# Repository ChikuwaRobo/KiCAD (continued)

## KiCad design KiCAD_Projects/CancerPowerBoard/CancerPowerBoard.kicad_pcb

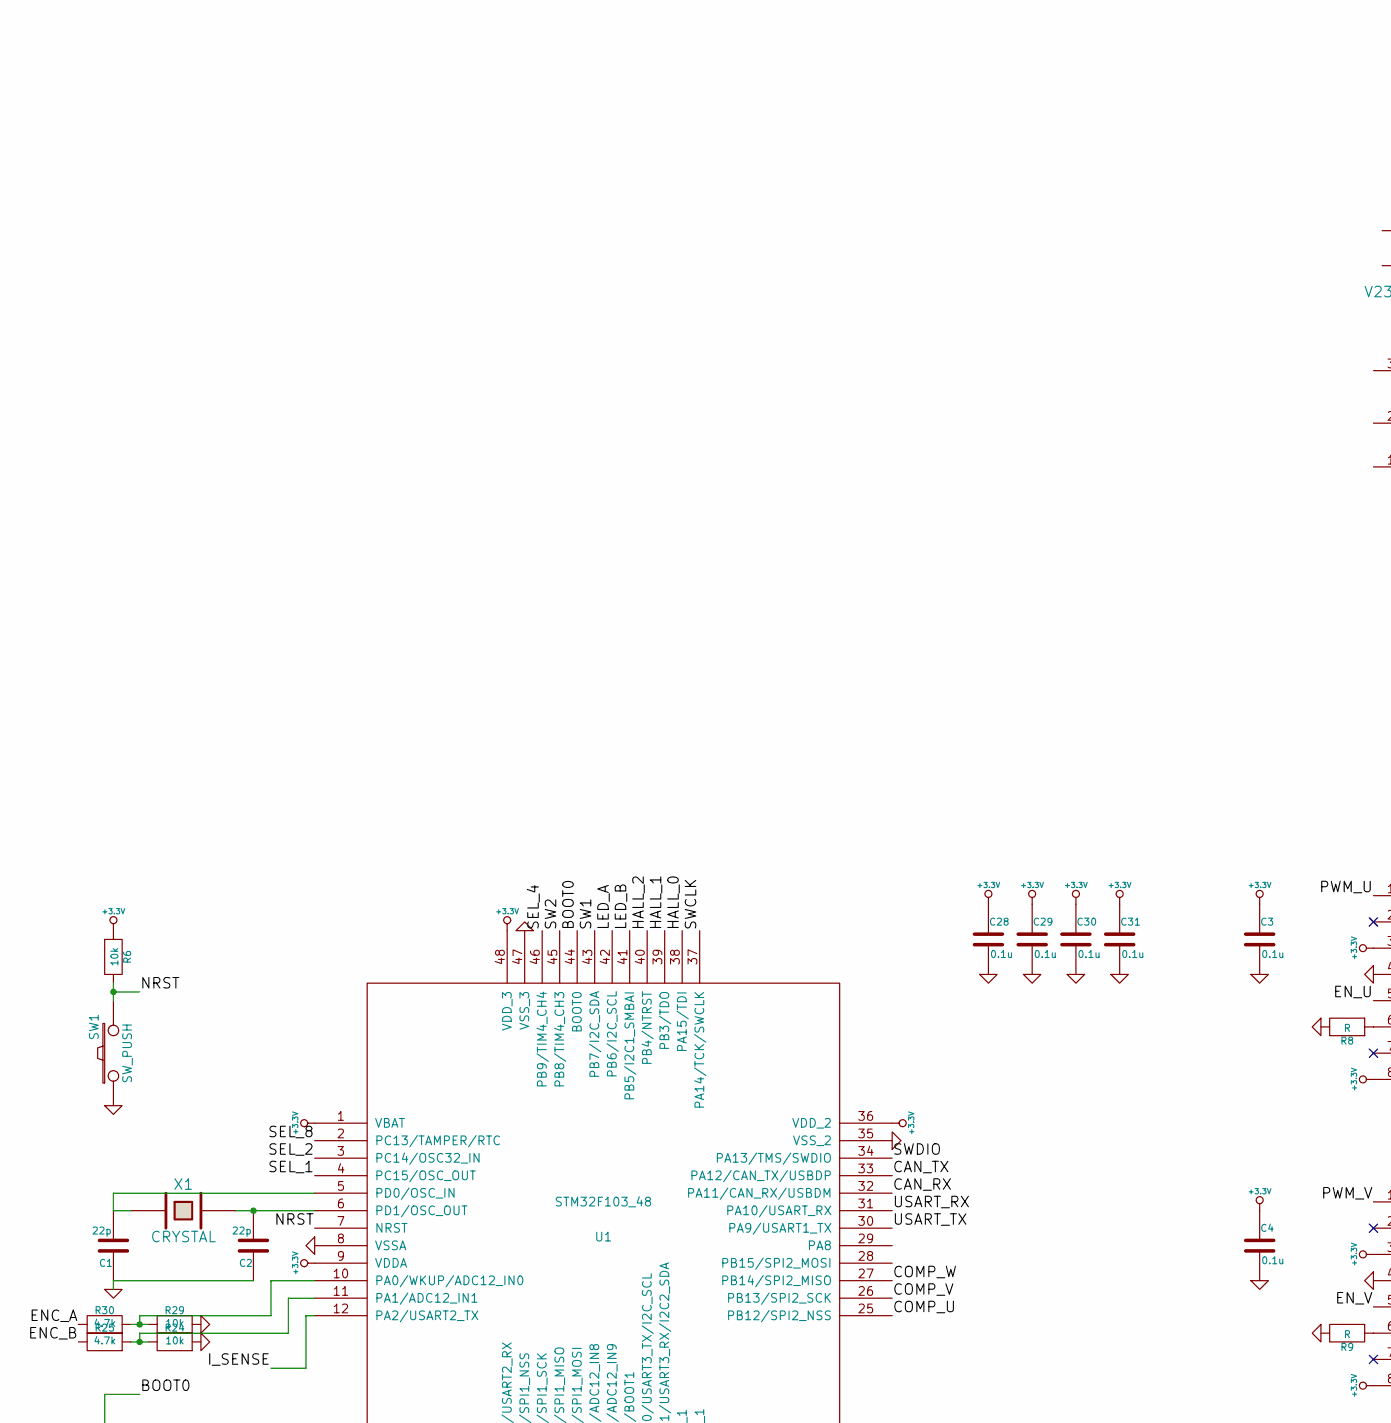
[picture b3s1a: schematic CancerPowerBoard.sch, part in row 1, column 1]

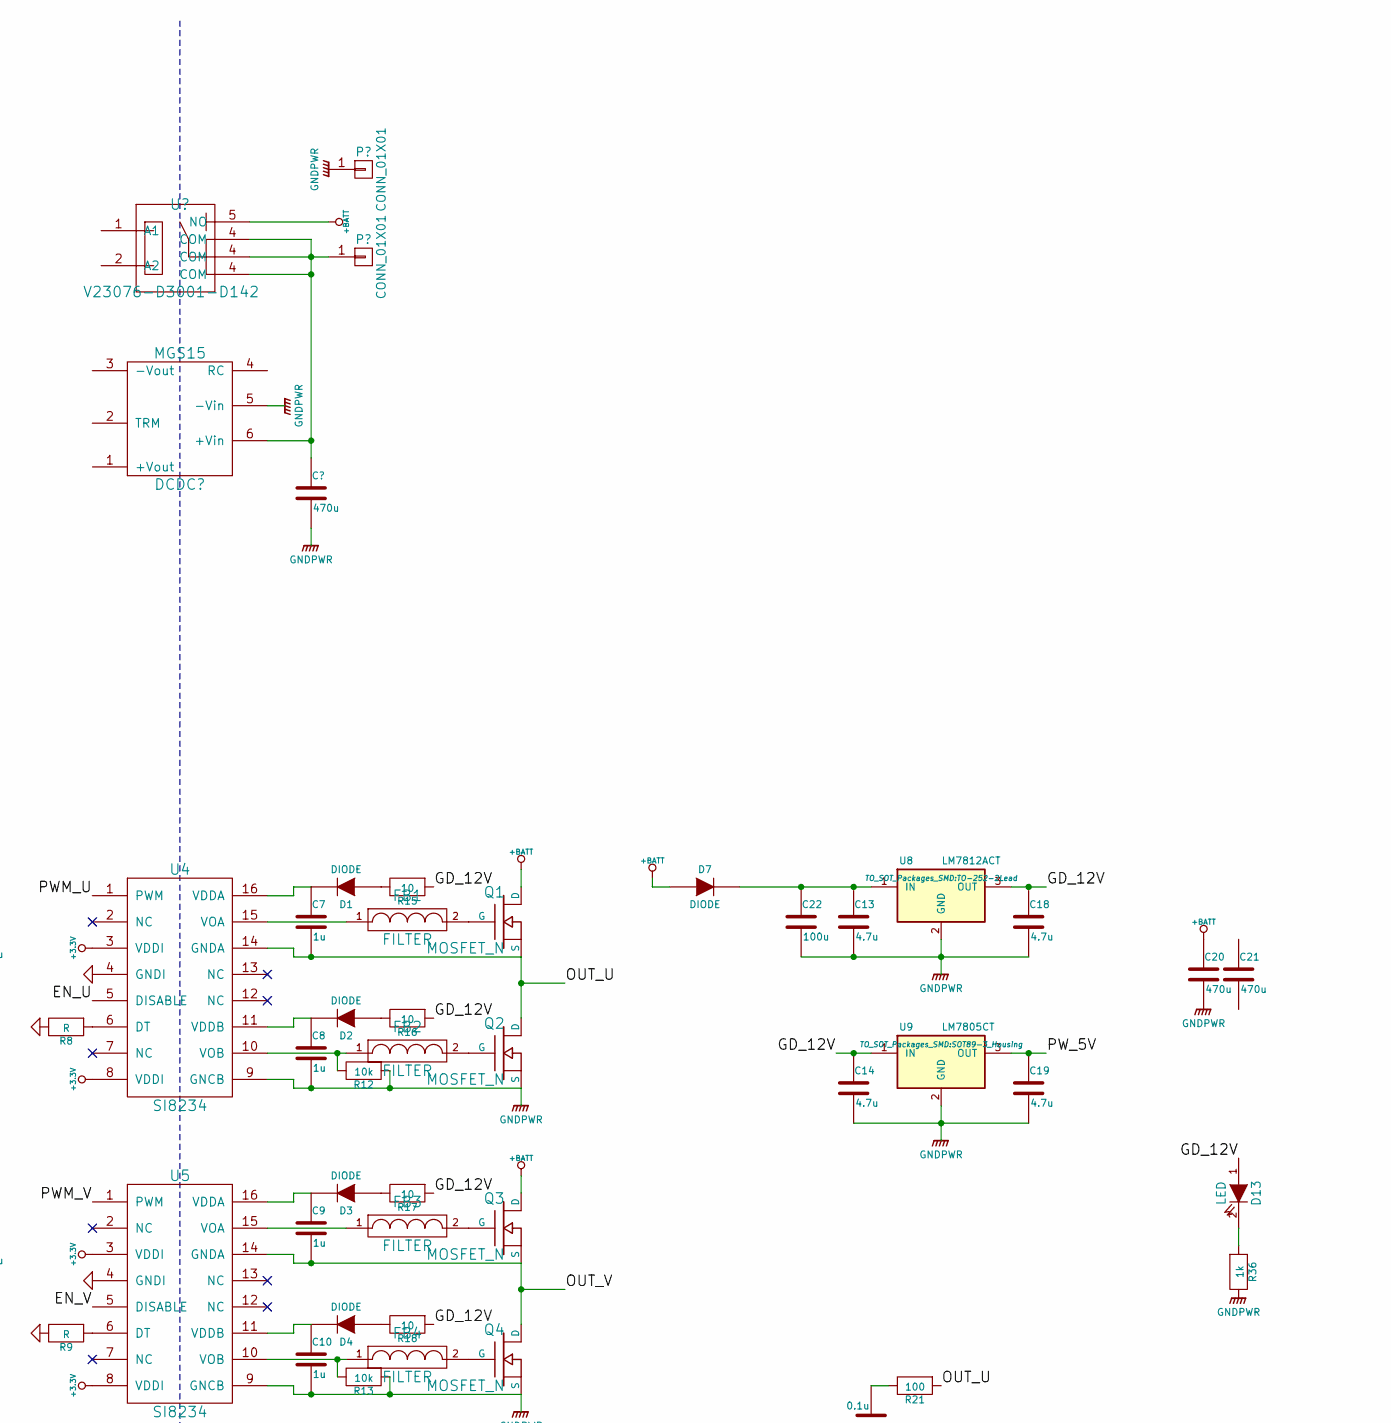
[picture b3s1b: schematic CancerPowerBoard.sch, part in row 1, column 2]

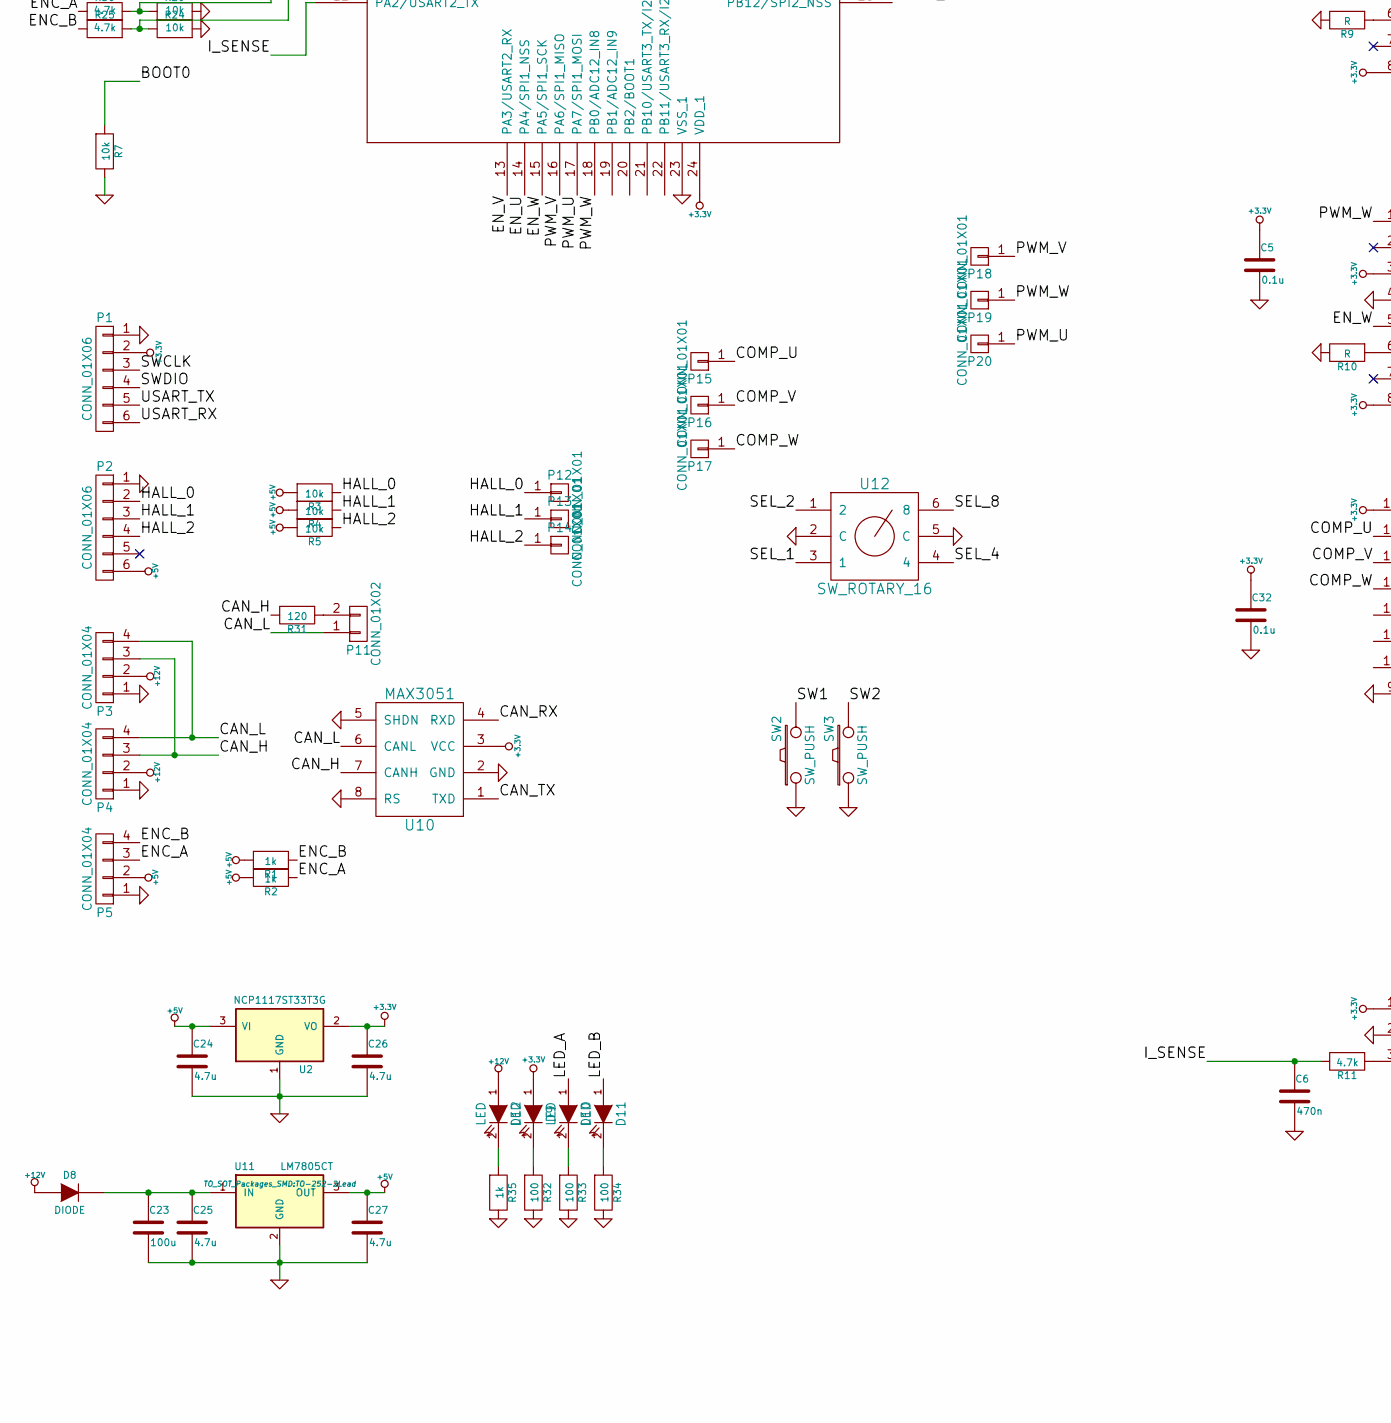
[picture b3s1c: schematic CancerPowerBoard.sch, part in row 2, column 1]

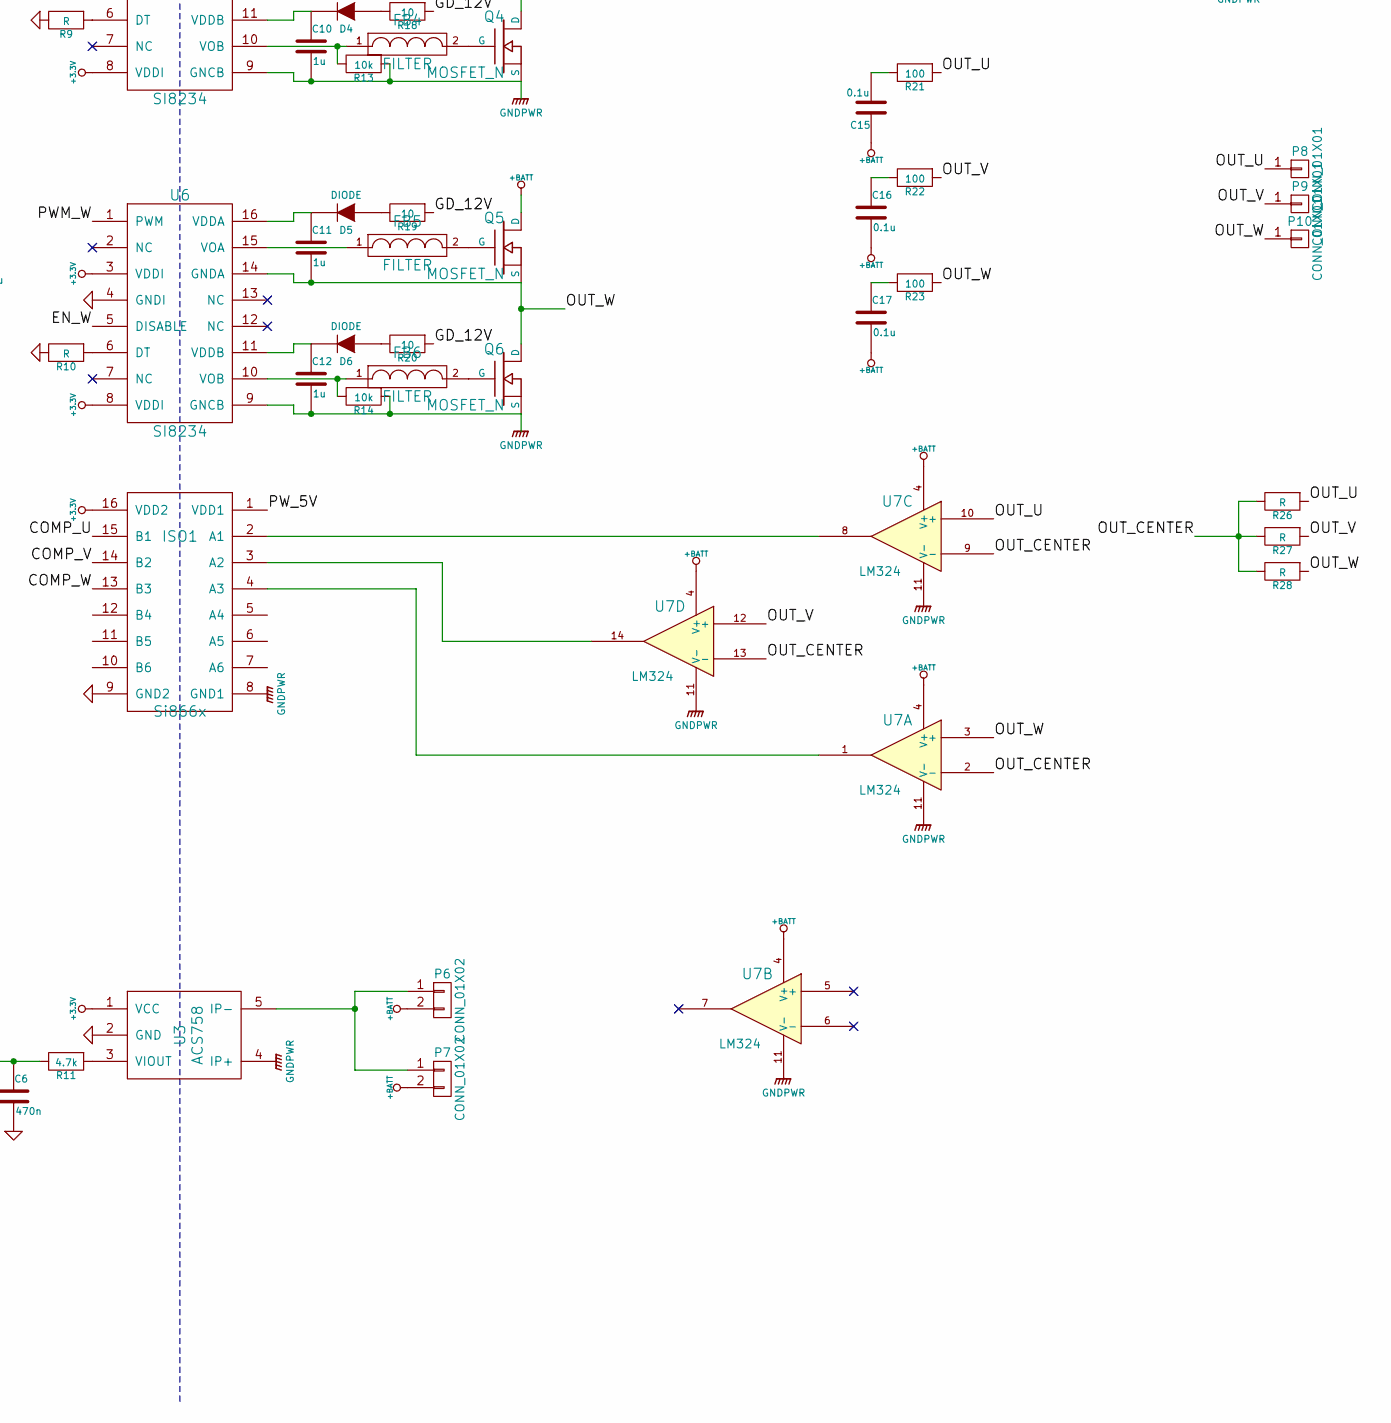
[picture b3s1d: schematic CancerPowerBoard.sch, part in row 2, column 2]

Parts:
C1, C2: 22p; C1608_WP
C3, C4, C5, C15, C16, C17, C28, C29, C30, C31, C32: 0.1u; C1608_WP
C6: 470n; C1608_WP
C7, C8, C9, C10, C11, C12: 1u; C3216
C13, C14, C18, C19, C24, C25, C26, C27: 4.7u; C3216
C20, C21: 470u; c_elec_10x10.5
C22, C23: 100u; C_Radial_D6.3_L11.2_P2.5
D1, D2, D3, D4, D5, D6: DIODE; C1608_WP
D7, D8: DIODE; C3216
D9, D10, D11, D12, D13: LED; LED_0805
FB1, FB2, FB3, FB4, FB5, FB6: FILTER; C1608_WP
ISO1: Si866x; SOIC-16_3.9x9.9mm_Pitch1.27mm
P1, P2: CONN_01X06; ZH_6T
P3, P4, P5: CONN_01X04; XA_4LC
P6: CONN_01X02; DEANS_T_F
P7: CONN_01X02; DEANS_T_M
P8, P9, P10: CONN_01X01; 1pin
P11: CONN_01X02; Pin_Header_Straight_1x02
P12, P13, P14, P15, P16, P17, P18, P19, P20: CONN_01X01; PINTST
Q1, Q2, Q3, Q4, Q5, Q6: MOSFET_N; HSOF-8-1
R1, R2, R35, R36: 1k; C1608_WP
R3, R4, R5, R6, R7, R12, R13, R14, R24, R29: 10k; C1608_WP
R8, R9, R10, R26, R27, R28: R; C1608_WP
R11, R25, R30: 4.7k; C1608_WP
R15, R16, R17, R18, R19, R20: 10; C1608_WP
R21, R22, R23, R32, R33, R34: 100; C1608_WP
R31: 120; C1608_WP
SW1, SW2, SW3: SW_PUSH; RP_SMD_Button
U1: STM32F103_48; LQFP-48_7x7mm_Pitch0.5mm
U2: NCP1117ST33T3G; SOT89-3_Housing
U3: ACS758; ACS785xCB
U4, U5, U6: SI8234; SOIC-16_3.9x9.9mm_Pitch1.27mm
U7: LM324; SSOP-14_5.3x6.2mm_Pitch0.65mm
U8: LM7812ACT; TO-252-2Lead
U9: LM7805CT; SOT89-3_Housing
U10: MAX3051; SOIC-8_3.9x4.9mm_Pitch1.27mm
U11: LM7805CT; TO-252-2Lead
U12: SW_ROTARY_16; rotary_0F
X1: CRYSTAL; ABM3_2pads

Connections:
+3.3V: C3.1, C4.1, C5.1, C26.1, C28.1, C29.1, C30.1, C31.1, C32.1, D9.1 (A), ISO1.16 (VDD2), P1.2, R6.1, U1.1 (VBAT), U1.9 (VDDA), U1.24 (VDD_1), U1.36 (VDD_2), U1.48 (VDD_3), U2.2 (VO), U3.1 (VCC), U4.3 (VDDI), U4.8 (VDDI), U5.3 (VDDI), U5.8 (VDDI), U6.3 (VDDI), U6.8 (VDDI), U10.3 (VCC)
+5V: C24.1, C27.1, P2.6, P5.2, R1.1, R2.1, R3.1, R4.1, R5.1, U2.3 (VI), U11.3 (OUT)
+12V: D8.2 (A), D12.1 (A), P3.2, P4.2
+BATT: C15.1, C16.2, C17.2, C20.1, C21.1, D7.2 (A), P6.2, P7.2, Q1.D, Q3.D, Q5.D, U7.4 (V+)
/BOOT0: R7.1, U1.44 (BOOT0)
/CAN_H: P3.3, P4.3, R31.2, U10.7 (CANH)
/CAN_L: P3.4, P4.4, P11.1, U10.6 (CANL)
/CAN_RX: U1.32 (PA11/CAN_RX/USBDM), U10.4 (RXD)
/CAN_TX: U1.33 (PA12/CAN_TX/USBDP), U10.1 (TXD)
/COMP_U: ISO1.15 (B1), P15.1, U1.25 (PB12/SPI2_NSS)
/COMP_V: ISO1.14 (B2), P16.1, U1.26 (PB13/SPI2_SCK)
/COMP_W: ISO1.13 (B3), P17.1, U1.27 (PB14/SPI2_MISO)
/ENC_A: P5.3, R2.2, R30.2
/ENC_B: P5.4, R1.2, R25.2
/EN_U: U1.14 (PA4/SPI1_NSS), U4.5 (DISABLE)
/EN_V: U1.13 (PA3/USART2_RX), U5.5 (DISABLE)
/EN_W: U1.15 (PA5/SPI1_SCK), U6.5 (DISABLE)
/GD_12V: C14.1, C18.1, D13.1 (A), R15.1, R16.1, R17.1, R18.1, R19.1, R20.1, U8.3 (OUT), U9.1 (IN)
/HALL_0: P2.2, P12.1, R3.2, U1.38 (PA15/TDI)
/HALL_1: P2.3, P13.1, R4.2, U1.39 (PB3/TDO)
/HALL_2: P2.4, P14.1, R5.2, U1.40 (PB4/NTRST)
/I_SENSE: C6.1, R11.2, U1.12 (PA2/USART2_TX)
/LED_A: D10.1 (A), U1.42 (PB6/I2C_SCL)
/LED_B: D11.1 (A), U1.41 (PB5/I2C1_SMBAI)
/NRST: R6.2, SW1.2, U1.7 (NRST)
/OUT_CENTER: R26.2, R27.2, R28.2, U7.2 (-), U7.9 (-), U7.13 (-)
/OUT_U: C7.2, P8.1, Q1.S, Q2.D, R21.1, R26.1, U4.14 (GNDA), U7.10 (+)
/OUT_V: C9.2, P9.1, Q3.S, Q4.D, R22.1, R27.1, U5.14 (GNDA), U7.12 (+)
/OUT_W: C11.2, P10.1, Q5.S, Q6.D, R23.1, R28.1, U6.14 (GNDA), U7.3 (+)
/PWM_U: P20.1, U1.17 (PA7/SPI1_MOSI), U4.1 (PWM)
/PWM_V: P18.1, U1.16 (PA6/SPI1_MISO), U5.1 (PWM)
/PWM_W: P19.1, U1.18 (PB0/ADC12_IN8), U6.1 (PWM)
/PW_5V: C19.1, ISO1.1 (VDD1), U9.3 (OUT)
/SEL_1: U1.4 (PC15/OSC_OUT), U12.3 (1)
/SEL_2: U1.3 (PC14/OSC32_IN), U12.1 (2)
/SEL_4: U1.46 (PB9/TIM4_CH4), U12.4
/SEL_8: U1.2 (PC13/TAMPER/RTC), U12.6 (8)
/SW1: SW2.2, U1.43 (PB7/I2C_SDA)
/SW2: SW3.2, U1.45 (PB8/TIM4_CH3)
/SWCLK: P1.3, U1.37 (PA14/TCK/SWCLK)
/SWDIO: P1.4, U1.34 (PA13/TMS/SWDIO)
/USART_RX: P1.6, U1.31 (PA10/USART_RX)
/USART_TX: P1.5, U1.30 (PA9/USART1_TX)
GND: C1.1, C2.1, C3.2, C4.2, C5.2, C6.2, C23.2, C24.2, C25.2, C26.2, C27.2, C28.2, C29.2, C30.2, C31.2, C32.2, ISO1.9 (GND2), P1.1, P2.1, P3.1, P4.1, P5.1, R7.2, R8.2, R9.2, R10.2, R24.1, R29.1, R32.2, R33.2, R34.2, R35.2, SW1.1, SW2.1, SW3.1, U1.8 (VSSA), U1.23 (VSS_1), U1.35 (VSS_2), U1.47 (VSS_3), U2.1 (GND), U3.2 (GND), U4.4 (GNDI), U5.4 (GNDI), U6.4 (GNDI), U10.2 (GND), U10.5 (SHDN), U10.8 (RS), U11.2 (GND), U12.2 (C), U12.5 (C)
GNDPWR: C8.2, C10.2, C12.2, C13.2, C14.2, C18.2, C19.2, C20.2, C21.2, C22.2, ISO1.8 (GND1), Q2.S, Q4.S, Q6.S, R12.1, R13.1, R14.1, R36.2, U3.4 (IP+), U4.9 (GNCB), U5.9 (GNCB), U6.9 (GNCB), U7.11 (V-), U8.2 (GND), U9.2 (GND)
unnamed: C1.2, U1.5 (PD0/OSC_IN), X1.1
unnamed: C2.2, U1.6 (PD1/OSC_OUT), X1.2
unnamed: C7.1, D1.1 (K), U4.16 (VDDA)
unnamed: C8.1, D2.1 (K), U4.11 (VDDB)
unnamed: C9.1, D3.1 (K), U5.16 (VDDA)
unnamed: C10.1, D4.1 (K), U5.11 (VDDB)
unnamed: C11.1, D5.1 (K), U6.16 (VDDA)
unnamed: C12.1, D6.1 (K), U6.11 (VDDB)
unnamed: C13.1, C22.1, D7.1 (K), U8.1 (IN)
unnamed: C15.2, R21.2
unnamed: C16.1, R22.2
unnamed: C17.1, R23.2
unnamed: C23.1, C25.1, D8.1 (K), U11.1 (IN)
unnamed: D1.2 (A), R15.2
unnamed: D2.2 (A), R16.2
unnamed: D3.2 (A), R17.2
unnamed: D4.2 (A), R18.2
unnamed: D5.2 (A), R19.2
unnamed: D6.2 (A), R20.2
unnamed: D9.2 (K), R32.1
unnamed: D10.2 (K), R33.1
unnamed: D11.2 (K), R34.1
unnamed: D12.2 (K), R35.1
unnamed: D13.2 (K), R36.1
unnamed: FB1.1, U4.15 (VOA)
unnamed: FB1.2, Q1.G
unnamed: FB2.1, R12.2, U4.10 (VOB)
unnamed: FB2.2, Q2.G
unnamed: FB3.1, U5.15 (VOA)
unnamed: FB3.2, Q3.G
unnamed: FB4.1, R13.2, U5.10 (VOB)
unnamed: FB4.2, Q4.G
unnamed: FB5.1, U6.15 (VOA)
unnamed: FB5.2, Q5.G
unnamed: FB6.1, R14.2, U6.10 (VOB)
unnamed: FB6.2, Q6.G
unnamed: ISO1.2 (A1), U7.8
unnamed: ISO1.3 (A2), U7.14
unnamed: ISO1.4 (A3), U7.1
unnamed: P6.1, P7.1, U3.5 (IP-)
unnamed: P11.2, R31.1
unnamed: R8.1, U4.6 (DT)
unnamed: R9.1, U5.6 (DT)
unnamed: R10.1, U6.6 (DT)
unnamed: R11.1, U3.3 (VIOUT)
unnamed: R24.2, R25.1, U1.11 (PA1/ADC12_IN1)
unnamed: R29.2, R30.1, U1.10 (PA0/WKUP/ADC12_IN0)

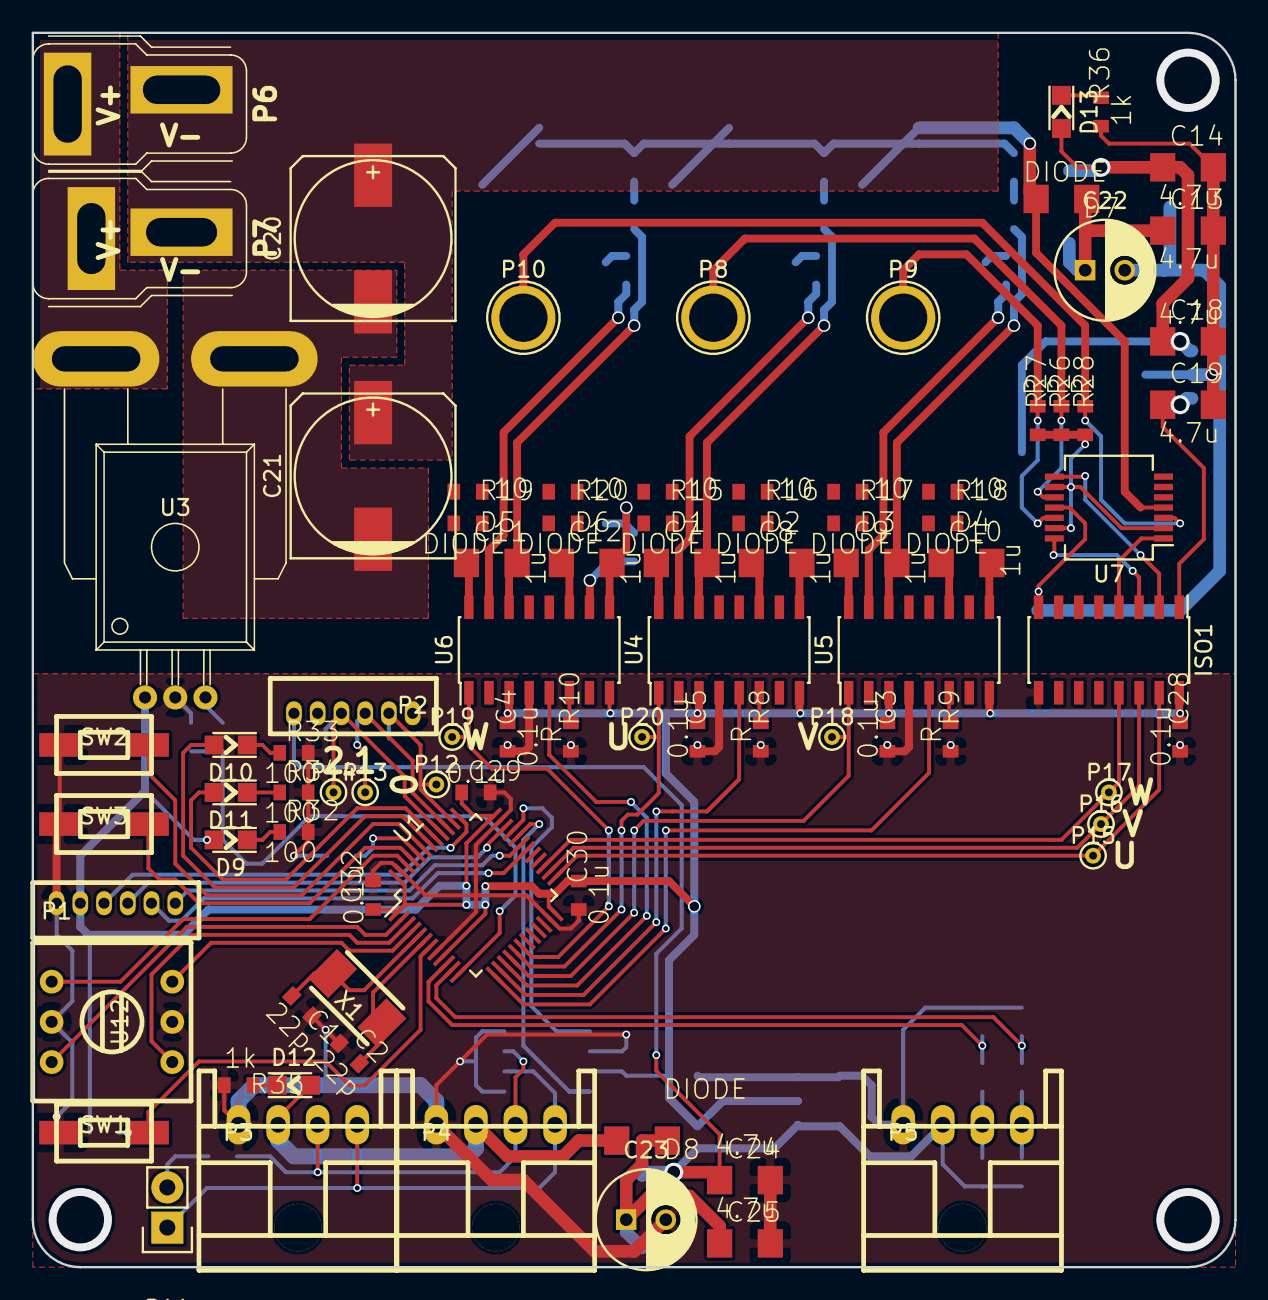
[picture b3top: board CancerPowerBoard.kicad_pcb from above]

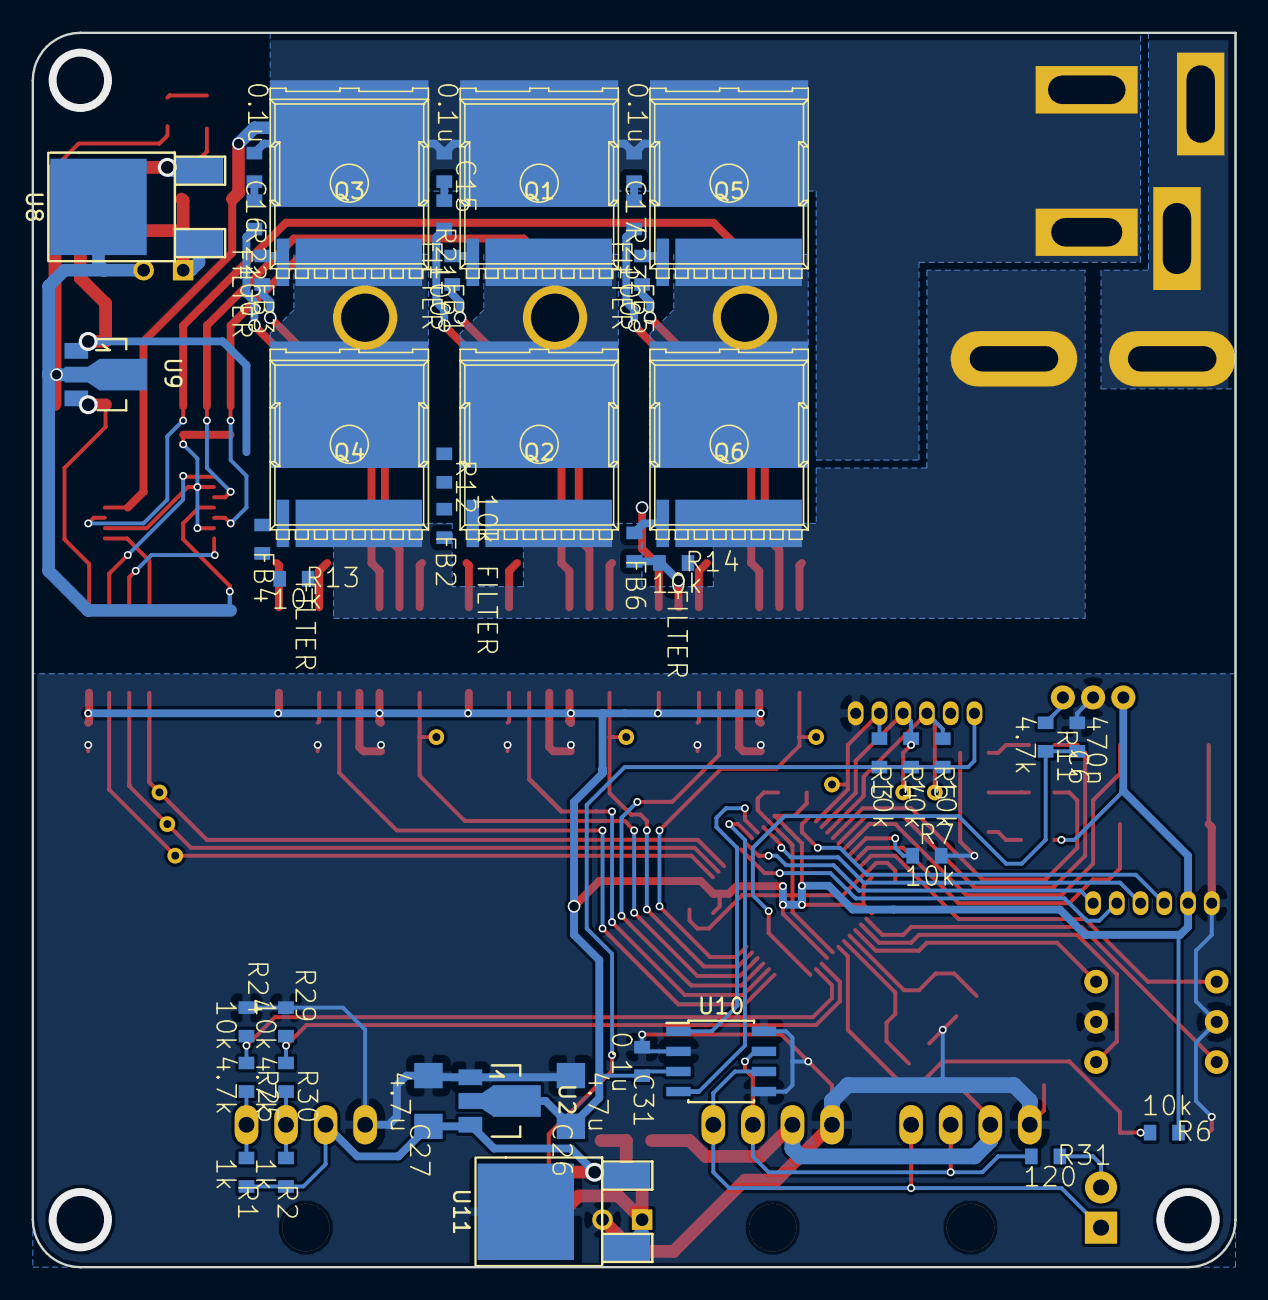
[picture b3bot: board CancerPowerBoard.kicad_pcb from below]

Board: 2 copper layers, 76.0 x 78.0 mm, 130 parts (43 on the bottom side), 92 nets.

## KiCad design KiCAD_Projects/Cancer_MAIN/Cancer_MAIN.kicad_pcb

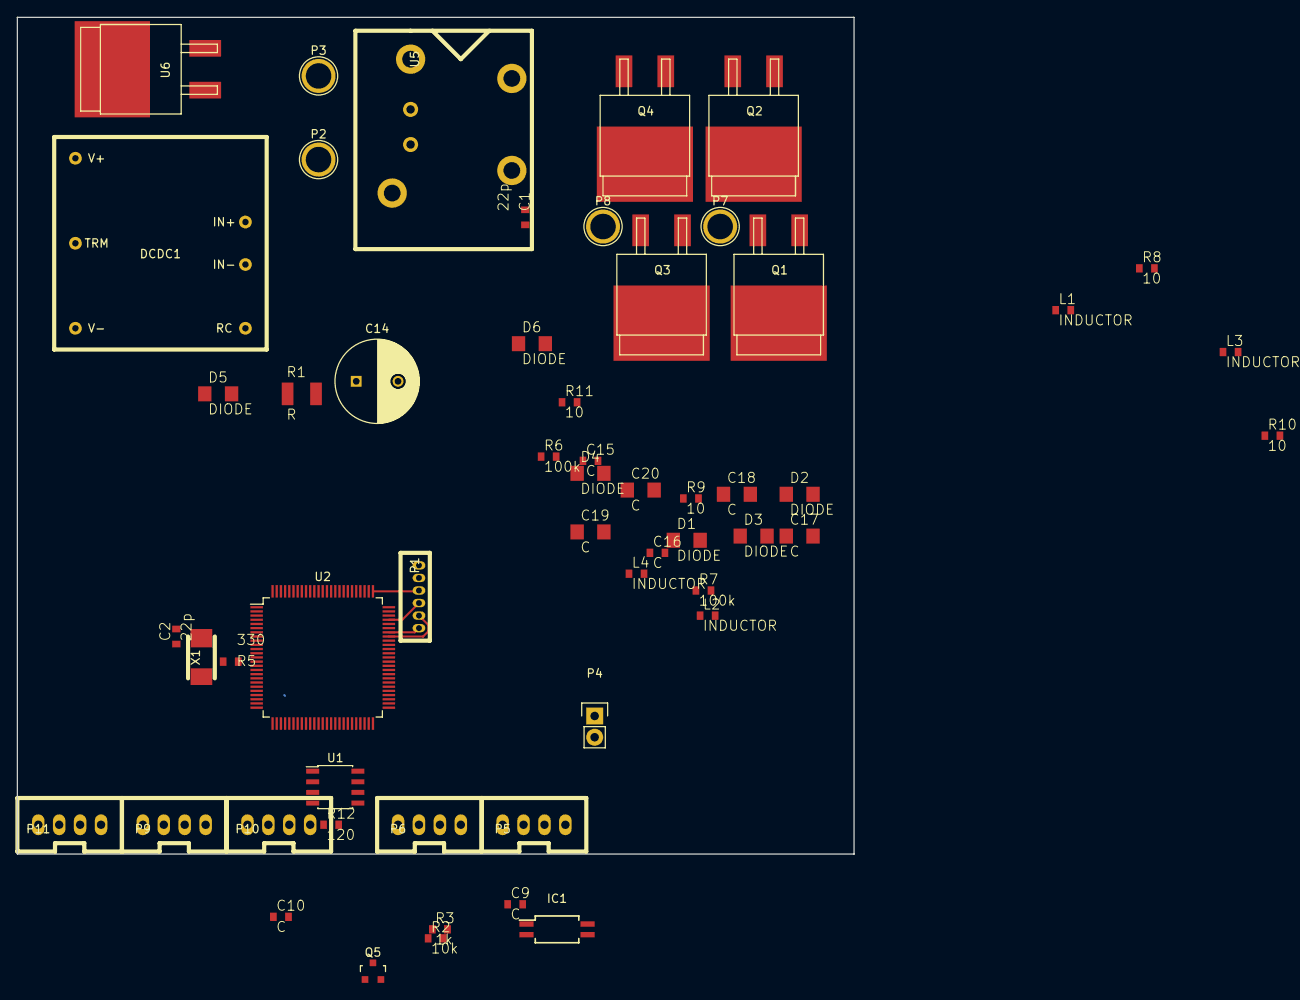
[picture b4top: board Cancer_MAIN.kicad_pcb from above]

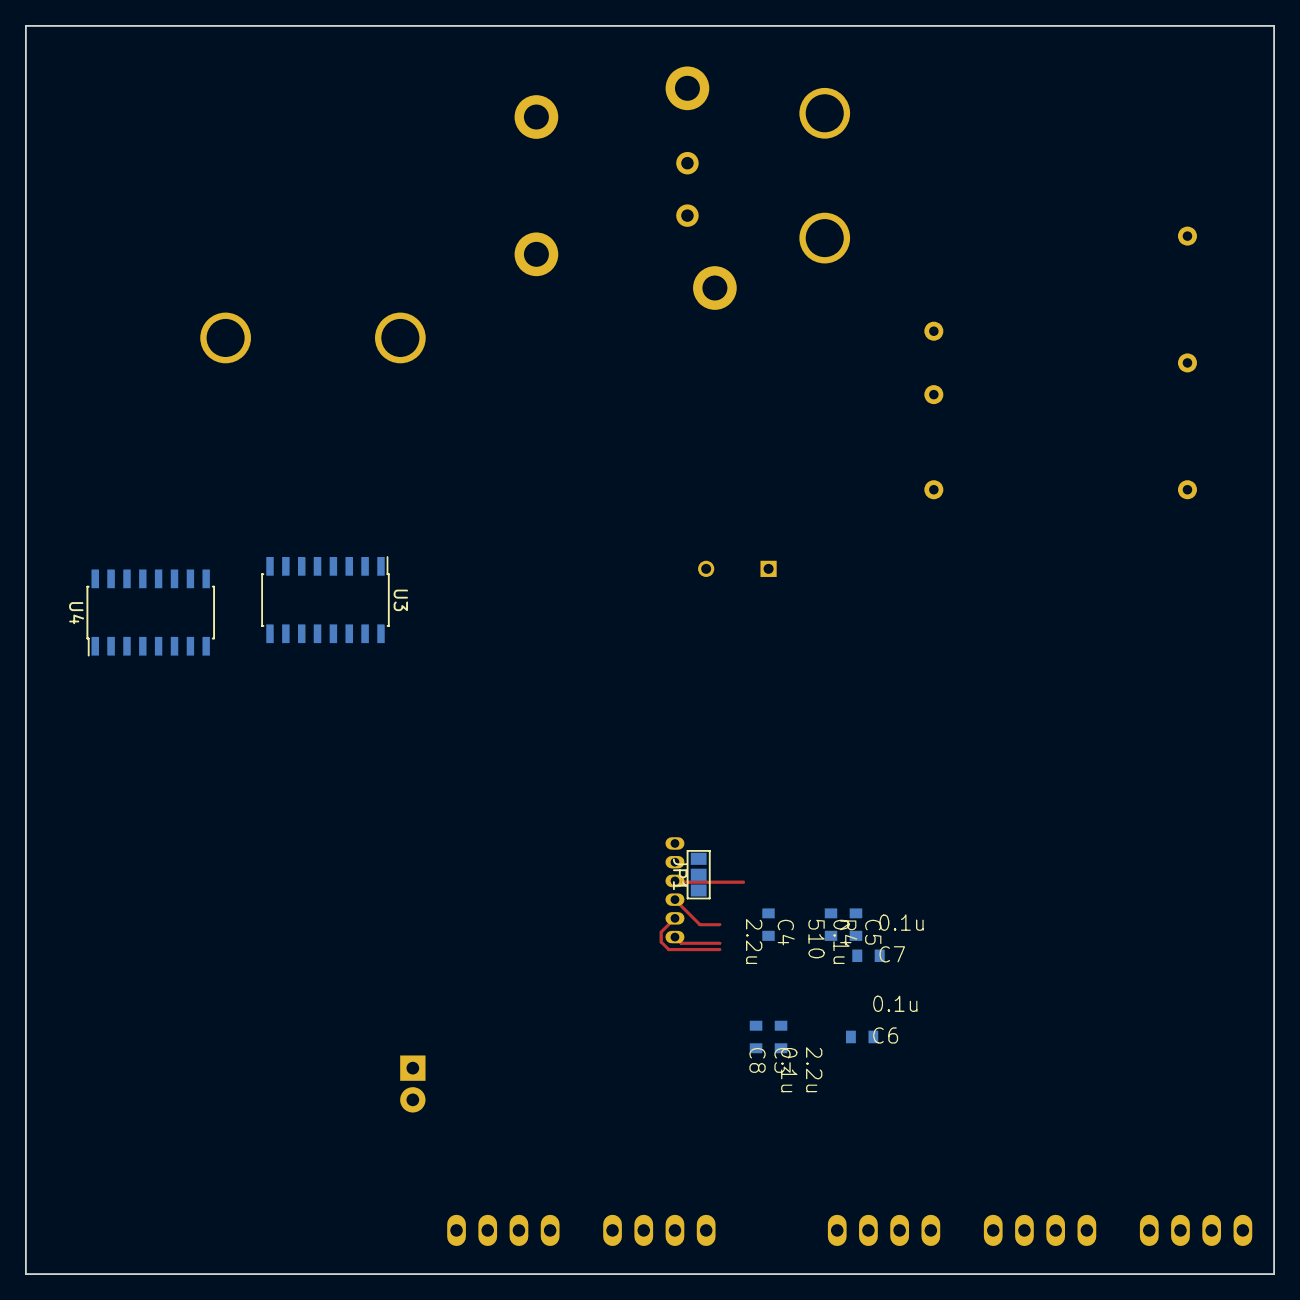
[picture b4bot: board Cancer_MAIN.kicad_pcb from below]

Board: 2 copper layers, 100.0 x 100.0 mm, 65 parts (10 on the bottom side), 54 nets.

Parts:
C1, C2: 22p; C1608_WP
C3, C4: 2.2u; C1608_WP
C5, C6, C7, C8: 0.1u; C1608_WP
C9, C10, C15, C16: C; C1608_WP
C14: C; C_Radial_D10_L20_P5
C17, C18, C19, C20: C; C3216
D1, D2, D3, D4, D5, D6: DIODE; C3216
DCDC1: MGS15
IC1: TLP291; SOIJ-4_5.3x5.3mm_Pitch1.27mm
JP1: JUMPER3; GS3
L1, L2, L3, L4: INDUCTOR; C1608_WP
P1: CONN_01X06; ZH_6T
P2, P3, P7, P8: CONN_01X01; 1pin
P4: CONN_01X02; Pin_Header_Straight_1x02
P5, P6, P9, P10, P11: CONN_01X04; XA_4T
Q1, Q2, Q3, Q4: MOSFET_N; D2-PAK
Q5: MOSFET_N; SOT-23
R1: R; C3225
R2: 10k; C1608_WP
R3: 1k; C1608_WP
R4: 510; C1608_WP
R5: 330; C1608_WP
R6, R7: 100k; C1608_WP
R8, R9, R10, R11: 10; C1608_WP
R12: 120; C1608_WP
U1: MAX3051; SOIC-8_3.9x4.9mm_Pitch1.27mm
U2: STM32F407VG; LQFP-100_14x14mm_Pitch0.5mm
U3, U4: SI8234; SOIC-16_3.9x9.9mm_Pitch1.27mm
U5: V23076-D3001-D142; V23076-A3001-D142
U6: MC78L12ACH; D2-PAK
X1: CRYSTAL; ABM3_2pads

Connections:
+3.3V: C5.1, C6.1, C7.1, C8.1, C15.2, C16.2, JP1.3, P9.2, P10.2, P11.2, U1.3, U2.6, U2.11, U2.19, U2.21, U2.22, U2.28, U2.50, U2.75, U2.100, U3.3, U3.8, U4.3, U4.8
+12V: DCDC1.1, P5.2, P6.2
+BATT: C14.1, P2.1, R1.2, U5.4
/BOOT0: R4.1, U2.94
/CANH: P4.2, P5.3, P6.3, U1.7
/CANL: P5.4, P6.4, R12.1, U1.6
/GD_12V: C10.1, D1.2, D2.2, D3.2, D4.2, D6.1, IC1.4, U5.1
/MD_EN: U3.5, U4.5
/NRST: JP1.1, U2.14
/OUT_A: C17.2, P7.1, Q1.S, Q2.D, U3.14
/OUT_B: C19.2, P8.1, Q3.S, Q4.D, U4.14
/POWER+: Q1.D, Q3.D, U5.5
/SWDCK: P1.3, U2.76
/SWDIO: P1.4, U2.72
/USART1_RX: P1.6, U2.69
/USART1_TX: P1.5, U2.68
/USART2_RX: P9.4, U2.26
/USART2_TX: P9.3, U2.25
/USART3_RX: P10.4, U2.56
/USART3_TX: P10.3, U2.55
/USART4_RX: P11.4, U2.79
/USART4_TX: P11.3, U2.78
GND: C1.1, C2.1, C3.2, C4.2, C5.2, C6.2, C7.2, C8.2, C15.1, C16.1, DCDC1.3, P1.1, P5.1, P6.1, P9.1, P10.1, P11.1, R4.2, R6.2, R7.2, U1.2, U1.5, U1.8, U2.10, U2.20, U2.27, U2.74, U2.99, U3.4, U4.4
GNDPWR: C9.2, C10.2, C14.2, C18.2, C20.2, P3.1, Q2.S, Q4.S, R2.2, U3.9, U4.9
unnamed: C1.2, R5.2, X1.2
unnamed: C2.2, U2.13, X1.1
unnamed: C3.1, U2.49
unnamed: C4.1, U2.73
unnamed: C9.1, D5.1
unnamed: C17.1, D1.1, U3.16
unnamed: C18.1, D2.1, U3.11
unnamed: C19.1, D3.1, U4.16
unnamed: C20.1, D4.1, U4.11
unnamed: D5.2, R1.1
unnamed: D6.2, U5.2
unnamed: IC1.3, R3.1
unnamed: JP1.2, P1.2
unnamed: L1.1, R8.1
unnamed: L1.2, Q1.G
unnamed: L2.1, R9.1
unnamed: L2.2, Q2.G
unnamed: L3.1, R10.1
unnamed: L3.2, Q3.G
unnamed: L4.1, R11.1
unnamed: L4.2, Q4.G
unnamed: P4.1, R12.2
unnamed: R2.1, R3.2
unnamed: R5.1, U2.12
unnamed: R6.1, U3.6
unnamed: R7.1, U4.6
unnamed: R8.2, U3.15
unnamed: R9.2, U3.10
unnamed: R10.2, U4.15
unnamed: R11.2, U4.10
